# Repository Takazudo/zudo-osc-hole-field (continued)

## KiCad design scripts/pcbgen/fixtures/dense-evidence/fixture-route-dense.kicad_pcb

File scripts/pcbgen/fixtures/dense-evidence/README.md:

# Dense routing repair work note

Issue #53 requires a complete 211-footprint, 30-cell, four-layer routing fixture with zero KiCad rule errors, schematic parity issues, and unconnected items after refill. Hardware centres and existing copper remain fixed. This remains an unvalidated synthetic draft, not an indicator circuit or fabrication release.

The historical report is preserved in `historical-attempts.json`. Its board and raw DRC were absent from this checkout and all current worktrees. Reconstruction therefore starts from the committed fixture sources; new measurements do not retrospectively validate the historical attempt.

Baseline: `pnpm circuit:check` passed (manual inventory, 42 lines, no schematic/placement binding; pin-asset check performed). `bash scripts/checks/regen-all.sh` passed and produced no tracked changes. Relevant owner mappings were read: WQP518MA S/T/TN remain CAD labels with exact terminal mapping UNSOURCED; OPA4196IDR uses its retained SOIC-14 pin map. No component evidence is changed here.

Diagnosis, repair, reproduction commands, and measured gates are recorded below as work completes.

## Diagnosis and recommendation

The new bounded reconstruction uses the same 211-footprint, four-layer, 30-cell slice and 40-pad connector. The historical C1607/J310 gaps could not be inspected without their missing board. In the reconstructed board those pads connect; the retained `baseline-drc.json` instead identifies seven GND connections, including C1907.2 at (134.8, 191.0) mm and C2907.2 at (151.8, 191.0) mm in the KiCad frame. The In1.Cu ground fill fractured into six polygons around connector escape tracks. Freerouting's five remaining connections became seven after the authoritative KiCad refill. Its three newly generated GND vias also violated the existing 0.25 mm clearance.

The adopted draft strategy keeps the In1.Cu GND plane and In2.Cu +12 V plane and adds a full-connect F.Cu GND pour. Existing ground through pads and vias join the fragmented inner-plane regions through the front pour. Two 0.7 mm / 0.3 mm ground vias connect the isolated capacitor pads. C2907's via requires a short 0.2 mm INPUT_20 detour on In1.Cu; the original new signal route ran directly under that ground pad. Three new router vias move 0.05–0.10 mm away from signal tracks, with their attached new GND segment endpoints following. `routing-corrections.json` retains the eight original/repaired copper records. All 1,080 pre-existing replicated track/via records are unchanged, verified by `preservation.json`.

No clearance, track-width, via or fixed-hardware targets were relaxed. The original track minimum remains 0.1 mm, ground clearance 0.25 mm, and four-layer stack unchanged. There is no added layer, blind/buried via, moved component, suppressed DRC category, or electrical qualification claim.

Alternatives considered: repeating the router timeout would not repair the observed plane fragmentation; a capacitor escape above/below C2907 collides with existing DRIVE/INPUT tracks. Short KiCad-only geometry trials and their failures are retained in `repair-attempts.json`. The accepted detour changes only new router geometry. Via-in-pad construction and the added front copper need eventual assembly/thermal review; this fixture proves only draft geometric routing.

## Reproduction and ownership

Run `bash scripts/pcbgen/test_route.sh --dense`. It enters the machine-wide guard, generates the complete schematic/netlist, syncs and places all footprints, replays `copper.json` and `stitching.json`, applies the source-defined planes, refills, and checks the complete KiCad 10.0.6 gate. The manifests are explicit retained routing sources, not a claim that the heuristic router is deterministic. Their pad-geometry fingerprint rejects a changed footprint, net, position, or side. Existing source copper must match exactly; unrelated owner objects are retained.

The pipeline checks DRC after source copper/planes are prepared and skips Freerouting when that complete gate already passes. A connectivity-complete rerun with a rule or parity error fails. A sync identity comparison now converts KiCad wxString library identifiers to Python text; otherwise an unchanged back-side footprint was replaced and flipped again on every regeneration.

`--dense-route` is an optional fresh bounded heuristic experiment. It archives earlier cache attempts, runs source-column routing and replication, then the full slice. It does not overwrite accepted evidence or claim completion unless the complete gate passes. The accepted solution is reproduced without any new heuristic router invocation.

The test also checks a second full generation, rejects stale copper and moved pads, retains an unrelated owner graphic, and removes C2907's required ground via on a disposable copy to verify that KiCad reports the missing GND connection. The checked-in PCB is retained for review; recreate its companion schematic/project through the reproduction command before schematic-parity inspection. No fabrication files are produced.

Physical circuit behavior, installed mechanical fit, current/thermal performance, via-in-pad assembly suitability, and fabrication qualification: **NOT RUN** — this is a synthetic routing fixture with no physical specimen or released manufacturing process.

KiCad serializes tracks/vias using transient net codes, so a reload can reorder identical copper objects. The fixture's final serialization sorts only source-owned copper slots by kind and retained UUID; owner objects and individual object bytes are preserved. This makes the first and subsequent complete source generation byte-identical. The normalizer does not change routes or DRC results.

## Original repair measurements (historical)

- Pinned KiCad 10.0.6: 0 rule errors, 0 unconnected items, 0 schematic parity issues; 159 warnings (80 silk-over-copper, 79 silk-overlap), unsuppressed.
- Complete fixture: 211 footprints, 30 selected locked hardware centres, 40 connector pads, four copper layers, 2,001 tracks and 208 vias. All 1,080 original replicated copper records match their retained fingerprint.
- `bash scripts/pcbgen/test_route.sh --dense`: **PASS**; guard `verdict=PASS`, 38 seconds execution, 7,045 MB minimum available host memory. Fresh rebuild and second full generation are byte-identical. No heuristic router invoked during replay.
- Missing C2907 stitch regression: exactly one GND disconnection, no rule errors. Changed placement/copper are rejected; an owner graphic is preserved.
- Host PCB/region/router unit tests: 15 passed. `pnpm circuit:check`: PASS; manual inventory has 42 lines, no schematic/placement binding, pin-asset check performed. Baseline `regen-all.sh` passed with no tracked drift.
- Fresh bounded heuristic evidence: source column 59.638 router seconds / 633.0 MB sampled peak; full slice 266.266 router seconds / 734.7 MB sampled peak. Both incomplete results are retained; the repaired replay is a separate successful result.
- Visual inspection: front ground continuity, inner connector escapes/plane cuts, and bottom repeated-cell routing inspected from KiCad layer plots. This is a visual geometry review, not hardware qualification.

The verification receipt binds the accepted board, final DRC/statistics, copper sources, board definition, and placement lock by SHA-256. `python3 scripts/pcbgen/fixtures/write_dense_report.py --check` checks those inputs and the generated acceptance summary. Replacing any of them requires renewed oracle evidence.

## Current-source replay and routing gate repair

The 2026-10-02 replay regenerated the fixture from current sources after the board definition's power-domain name changed from `J` to `JL`. The earlier receipt was stale and was not accepted by updating hashes alone. Fresh pinned KiCad execution passed, and only then were the retained board, DRC, statistics, native ratsnest, routing report, run log and verification receipt replaced. Historical failed router attempts and repair records remain unchanged.

The current replay retains the same 211 footprints, 30 fixed hardware centres, 40 connector pads, four layers, 2,001 tracks, 208 vias, and 1,080 original copper records. Native results are 0 rule errors, 0 schematic parity issues, 0 unconnected items and 0 native open edges, with 159 warnings. `final-routing.json` and `final-ratsnest.json` bind the exact final canonical board bytes. The second full generation remains byte-identical. A disposable copy with weakened project clearance/width rules is repaired from the current board definition before native DRC; its copper bytes and unrelated project setting are preserved, and its next run is unchanged.

The retained log covers dense replay followed by bounded one/four/six-instance Freerouting checks and the deliberately unroutable timeout case. The combined machine guard reported PASS in 127 seconds with 6,709 MB minimum available memory. The quick successful fixtures had 0 rule errors, 0 parity issues and 0 unconnected items; the designated timeout retained seven native open edges and remained incomplete. These are software/geometry checks, not electrical or physical qualification.

The dense replay now runs in CI. Local and self-hosted runs require the machine-wide heavy guard; only a GitHub-hosted Actions job identified by both `GITHUB_ACTIONS=true` and `RUNNER_ENVIRONMENT=github-hosted` runs directly, because that job has its own runner and no user-local guard installation. Wrapper dispatch regressions cover missing, partial and self-hosted environment values. No bypass was used for these local native runs.

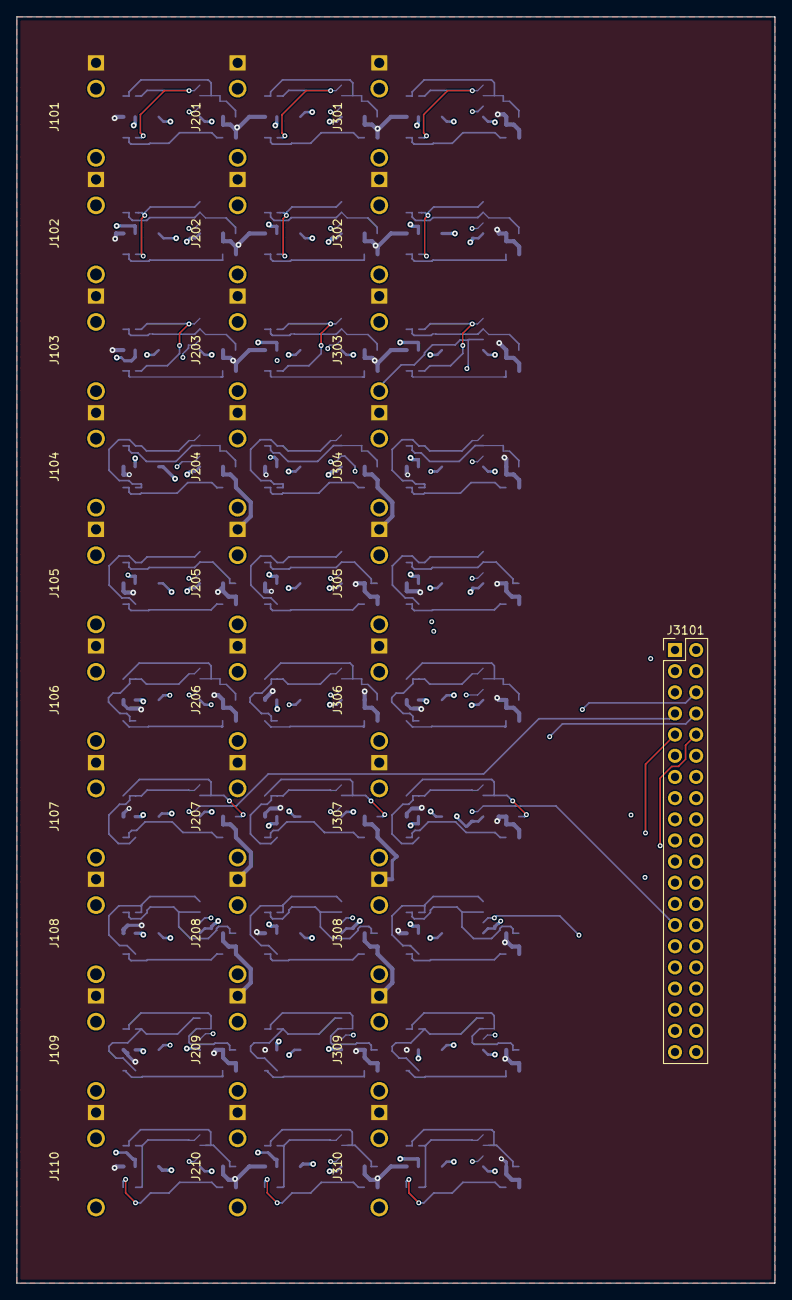
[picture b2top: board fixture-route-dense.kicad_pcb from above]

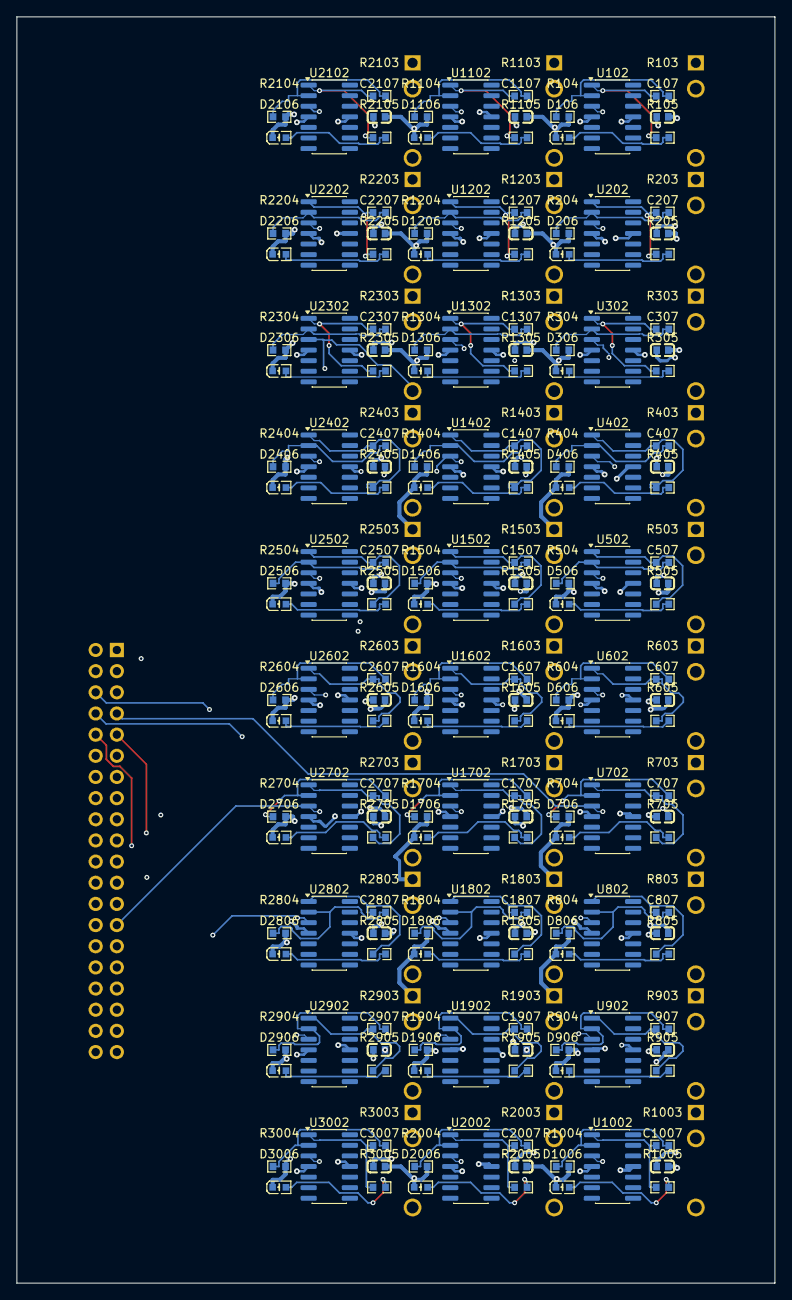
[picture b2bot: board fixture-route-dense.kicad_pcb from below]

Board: 4 copper layers, 91.0 x 152.0 mm, 211 parts (180 on the bottom side), 123 nets.

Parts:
C107, C207, C307, C407, C507, C607, C707, C807, C907, C1007, C1107, C1207, C1307, C1407, C1507, C1607, C1707, C1807, C1907, C2007, C2107, C2207, C2307, C2407, C2507, C2607, C2707, C2807, C2907, C3007: GRM188R71H104KA93D; C0603
D106, D206, D306, D406, D506, D606, D706, D806, D906, D1006, D1106, D1206, D1306, D1406, D1506, D1606, D1706, D1806, D1906, D2006, D2106, D2206, D2306, D2406, D2506, D2606, D2706, D2806, D2906, D3006: 0603Whitelight_C2290; LED0603-R-RD_WHITE
J101, J102, J103, J104, J105, J106, J107, J108, J109, J110, J201, J202, J203, J204, J205, J206, J207, J208, J209, J210, J301, J302, J303, J304, J305, J306, J307, J308, J309, J310: WQP518MA; Jack_3.5mm_QingPu_WQP518MA
J3101: Conn_02x20_Odd_Even; PinHeader_2x20_P2.54mm_Vertical
R103, R104, R105, R203, R204, R205, R303, R304, R305, R403, R404, R405, R503, R504, R505, R603, R604, R605, R703, R704, R705, R803, R804, R805, R903, R904, R905, R1003, R1004, R1005, R1103, R1104, R1105, R1203, R1204, R1205, R1303, R1304, R1305, R1403, R1404, R1405, R1503, R1504, R1505, R1603, R1604, R1605, R1703, R1704, R1705, R1803, R1804, R1805, R1903, R1904, R1905, R2003, R2004, R2005, R2103, R2104, R2105, R2203, R2204, R2205, R2303, R2304, R2305, R2403, R2404, R2405, R2503, R2504, R2505, R2603, R2604, R2605, R2703, R2704, R2705, R2803, R2804, R2805, R2903, R2904, R2905, R3003, R3004, R3005: RC0603FR-07100KL; R0603
U102, U202, U302, U402, U502, U602, U702, U802, U902, U1002, U1102, U1202, U1302, U1402, U1502, U1602, U1702, U1802, U1902, U2002, U2102, U2202, U2302, U2402, U2502, U2602, U2702, U2802, U2902, U3002: OPA4196IDR; SOIC-14_3.9x8.7mm_P1.27mm

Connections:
+12V: C107.1, C207.1, C307.1, C407.1, C507.1, C607.1, C707.1, C807.1, C907.1, C1007.1, C1107.1, C1207.1, C1307.1, C1407.1, C1507.1, C1607.1, C1707.1, C1807.1, C1907.1, C2007.1, C2107.1, C2207.1, C2307.1, C2407.1, C2507.1, C2607.1, C2707.1, C2807.1, C2907.1, C3007.1, U102.4, U202.4, U302.4, U402.4, U502.4, U602.4, U702.4, U802.4, U902.4, U1002.4, U1102.4, U1202.4, U1302.4, U1402.4, U1502.4, U1602.4, U1702.4, U1802.4, U1902.4, U2002.4, U2102.4, U2202.4, U2302.4, U2402.4, U2502.4, U2602.4, U2702.4, U2802.4, U2902.4, U3002.4
-12V: U102.11, U202.11, U302.11, U402.11, U502.11, U602.11, U702.11, U802.11, U902.11, U1002.11, U1102.11, U1202.11, U1302.11, U1402.11, U1502.11, U1602.11, U1702.11, U1802.11, U1902.11, U2002.11, U2102.11, U2202.11, U2302.11, U2402.11, U2502.11, U2602.11, U2702.11, U2802.11, U2902.11, U3002.11
/C1/DRIVE: R103.1, R105.1, U102.1
/C1/FB: R103.2, R104.1, U102.2
/C1/LED_A: D106.1, R105.2
/C2/DRIVE: R203.1, R205.1, U202.1
/C2/FB: R203.2, R204.1, U202.2
/C2/LED_A: D206.1, R205.2
/C3/DRIVE: R303.1, R305.1, U302.1
/C3/FB: R303.2, R304.1, U302.2
/C3/LED_A: D306.1, R305.2
/C4/DRIVE: R403.1, R405.1, U402.1
/C4/FB: R403.2, R404.1, U402.2
/C4/LED_A: D406.1, R405.2
/C5/DRIVE: R503.1, R505.1, U502.1
/C5/FB: R503.2, R504.1, U502.2
/C5/LED_A: D506.1, R505.2
/C6/DRIVE: R603.1, R605.1, U602.1
/C6/FB: R603.2, R604.1, U602.2
/C6/LED_A: D606.1, R605.2
/C7/DRIVE: R703.1, R705.1, U702.1
/C7/FB: R703.2, R704.1, U702.2
/C7/LED_A: D706.1, R705.2
/C8/DRIVE: R803.1, R805.1, U802.1
/C8/FB: R803.2, R804.1, U802.2
/C8/LED_A: D806.1, R805.2
/C9/DRIVE: R903.1, R905.1, U902.1
/C9/FB: R903.2, R904.1, U902.2
/C9/LED_A: D906.1, R905.2
/C10/DRIVE: R1003.1, R1005.1, U1002.1
/C10/FB: R1003.2, R1004.1, U1002.2
/C10/LED_A: D1006.1, R1005.2
/C11/DRIVE: R1103.1, R1105.1, U1102.1
/C11/FB: R1103.2, R1104.1, U1102.2
/C11/LED_A: D1106.1, R1105.2
/C12/DRIVE: R1203.1, R1205.1, U1202.1
/C12/FB: R1203.2, R1204.1, U1202.2
/C12/LED_A: D1206.1, R1205.2
/C13/DRIVE: R1303.1, R1305.1, U1302.1
/C13/FB: R1303.2, R1304.1, U1302.2
/C13/LED_A: D1306.1, R1305.2
/C14/DRIVE: R1403.1, R1405.1, U1402.1
/C14/FB: R1403.2, R1404.1, U1402.2
/C14/LED_A: D1406.1, R1405.2
/C15/DRIVE: R1503.1, R1505.1, U1502.1
/C15/FB: R1503.2, R1504.1, U1502.2
/C15/LED_A: D1506.1, R1505.2
/C16/DRIVE: R1603.1, R1605.1, U1602.1
/C16/FB: R1603.2, R1604.1, U1602.2
/C16/LED_A: D1606.1, R1605.2
/C17/DRIVE: R1703.1, R1705.1, U1702.1
/C17/FB: R1703.2, R1704.1, U1702.2
/C17/LED_A: D1706.1, R1705.2
/C18/DRIVE: R1803.1, R1805.1, U1802.1
/C18/FB: R1803.2, R1804.1, U1802.2
/C18/LED_A: D1806.1, R1805.2
/C19/DRIVE: R1903.1, R1905.1, U1902.1
/C19/FB: R1903.2, R1904.1, U1902.2
/C19/LED_A: D1906.1, R1905.2
/C20/DRIVE: R2003.1, R2005.1, U2002.1
/C20/FB: R2003.2, R2004.1, U2002.2
/C20/LED_A: D2006.1, R2005.2
/C21/DRIVE: R2103.1, R2105.1, U2102.1
/C21/FB: R2103.2, R2104.1, U2102.2
/C21/LED_A: D2106.1, R2105.2
/C22/DRIVE: R2203.1, R2205.1, U2202.1
/C22/FB: R2203.2, R2204.1, U2202.2
/C22/LED_A: D2206.1, R2205.2
/C23/DRIVE: R2303.1, R2305.1, U2302.1
/C23/FB: R2303.2, R2304.1, U2302.2
/C23/LED_A: D2306.1, R2305.2
/C24/DRIVE: R2403.1, R2405.1, U2402.1
/C24/FB: R2403.2, R2404.1, U2402.2
/C24/LED_A: D2406.1, R2405.2
/C25/DRIVE: R2503.1, R2505.1, U2502.1
/C25/FB: R2503.2, R2504.1, U2502.2
/C25/LED_A: D2506.1, R2505.2
/C26/DRIVE: R2603.1, R2605.1, U2602.1
/C26/FB: R2603.2, R2604.1, U2602.2
/C26/LED_A: D2606.1, R2605.2
/C27/DRIVE: R2703.1, R2705.1, U2702.1
/C27/FB: R2703.2, R2704.1, U2702.2
/C27/LED_A: D2706.1, R2705.2
/C28/DRIVE: R2803.1, R2805.1, U2802.1
/C28/FB: R2803.2, R2804.1, U2802.2
/C28/LED_A: D2806.1, R2805.2
/C29/DRIVE: R2903.1, R2905.1, U2902.1
/C29/FB: R2903.2, R2904.1, U2902.2
/C29/LED_A: D2906.1, R2905.2
/C30/DRIVE: R3003.1, R3005.1, U3002.1
/C30/FB: R3003.2, R3004.1, U3002.2
/C30/LED_A: D3006.1, R3005.2
GND: C107.2, C207.2, C307.2, C407.2, C507.2, C607.2, C707.2, C807.2, C907.2, C1007.2, C1107.2, C1207.2, C1307.2, C1407.2, C1507.2, C1607.2, C1707.2, C1807.2, C1907.2, C2007.2, C2107.2, C2207.2, C2307.2, C2407.2, C2507.2, C2607.2, C2707.2, C2807.2, C2907.2, C3007.2, D106.2, D206.2, D306.2, D406.2, D506.2, D606.2, D706.2, D806.2, D906.2, D1006.2, D1106.2, D1206.2, D1306.2, D1406.2, D1506.2, D1606.2, D1706.2, D1806.2, D1906.2, D2006.2, D2106.2, D2206.2, D2306.2, D2406.2, D2506.2, D2606.2, D2706.2, D2806.2, D2906.2, D3006.2, J101.S, J102.S, J103.S, J104.S, J105.S, J106.S, J107.S, J108.S, J109.S, J110.S, J201.S, J202.S, J203.S, J204.S, J205.S, J206.S, J207.S, J208.S, J209.S, J210.S, J301.S, J302.S, J303.S, J304.S, J305.S, J306.S, J307.S, J308.S, J309.S, J310.S, R104.2, R204.2, R304.2, R404.2, R504.2, R604.2, R704.2, R804.2, R904.2, R1004.2, R1104.2, R1204.2, R1304.2, R1404.2, R1504.2, R1604.2, R1704.2, R1804.2, R1904.2, R2004.2, R2104.2, R2204.2, R2304.2, R2404.2, R2504.2, R2604.2, R2704.2, R2804.2, R2904.2, R3004.2
INPUT_1: J101.T, J3101.1, U102.3
INPUT_2: J102.T, J3101.2, U202.3
INPUT_3: J103.T, J3101.3, U302.3
INPUT_4: J104.T, J3101.4, U402.3
INPUT_5: J105.T, J3101.5, U502.3
INPUT_6: J106.T, J3101.6, U602.3
INPUT_7: J107.T, J3101.7, U702.3
INPUT_8: J108.T, J3101.8, U802.3
INPUT_9: J109.T, J3101.9, U902.3
INPUT_10: J110.T, J3101.10, U1002.3
INPUT_11: J201.T, J3101.11, U1102.3
INPUT_12: J202.T, J3101.12, U1202.3
INPUT_13: J203.T, J3101.13, U1302.3
INPUT_14: J204.T, J3101.14, U1402.3
INPUT_15: J205.T, J3101.15, U1502.3
INPUT_16: J206.T, J3101.16, U1602.3
INPUT_17: J207.T, J3101.17, U1702.3
INPUT_18: J208.T, J3101.18, U1802.3
INPUT_19: J209.T, J3101.19, U1902.3
INPUT_20: J210.T, J3101.20, U2002.3
INPUT_21: J301.T, J3101.21, U2102.3
INPUT_22: J302.T, J3101.22, U2202.3
INPUT_23: J303.T, J3101.23, U2302.3
INPUT_24: J304.T, J3101.24, U2402.3
INPUT_25: J305.T, J3101.25, U2502.3
INPUT_26: J306.T, J3101.26, U2602.3
INPUT_27: J307.T, J3101.27, U2702.3
INPUT_28: J308.T, J3101.28, U2802.3
INPUT_29: J309.T, J3101.29, U2902.3
INPUT_30: J310.T, J3101.30, U3002.3
